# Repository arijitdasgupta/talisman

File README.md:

# Talisman

In at attempt to teach myself how to design PCBs, I made this trinket thingie to share with my friends. The board runs RP2040, and I am going to make some games for it.

## Games that run on this

 - [Bike w Friends](https://github.com/arijitdasgupta/bike_w_friends/)
 - [Flappy Mycologist](https://github.com/arijitdasgupta/flappy_mycologist)

## Features

 - I2C SSD1306 based display
 - Raspberry Pi Pico brain
 - 3 x buttons
 - Shared power between battery & USB
 - Battery charging
 - 3D printable case

## Notes

The manufacturing process with PCB makers such as JLCPCB is a little convoluted, even though I added BOM, drills and rotation files those may not be usable for you. But the general schematic designs and part ids should be helpful if you decide to make one yourself. If you have any questions, do drop a note. I have purposefully omitted writing a build guide for this very reason, but I am happy to write on up if anyone needs it.

## TODO
 - Write assembly instructions

## What's Friday Makers Club?

TODO

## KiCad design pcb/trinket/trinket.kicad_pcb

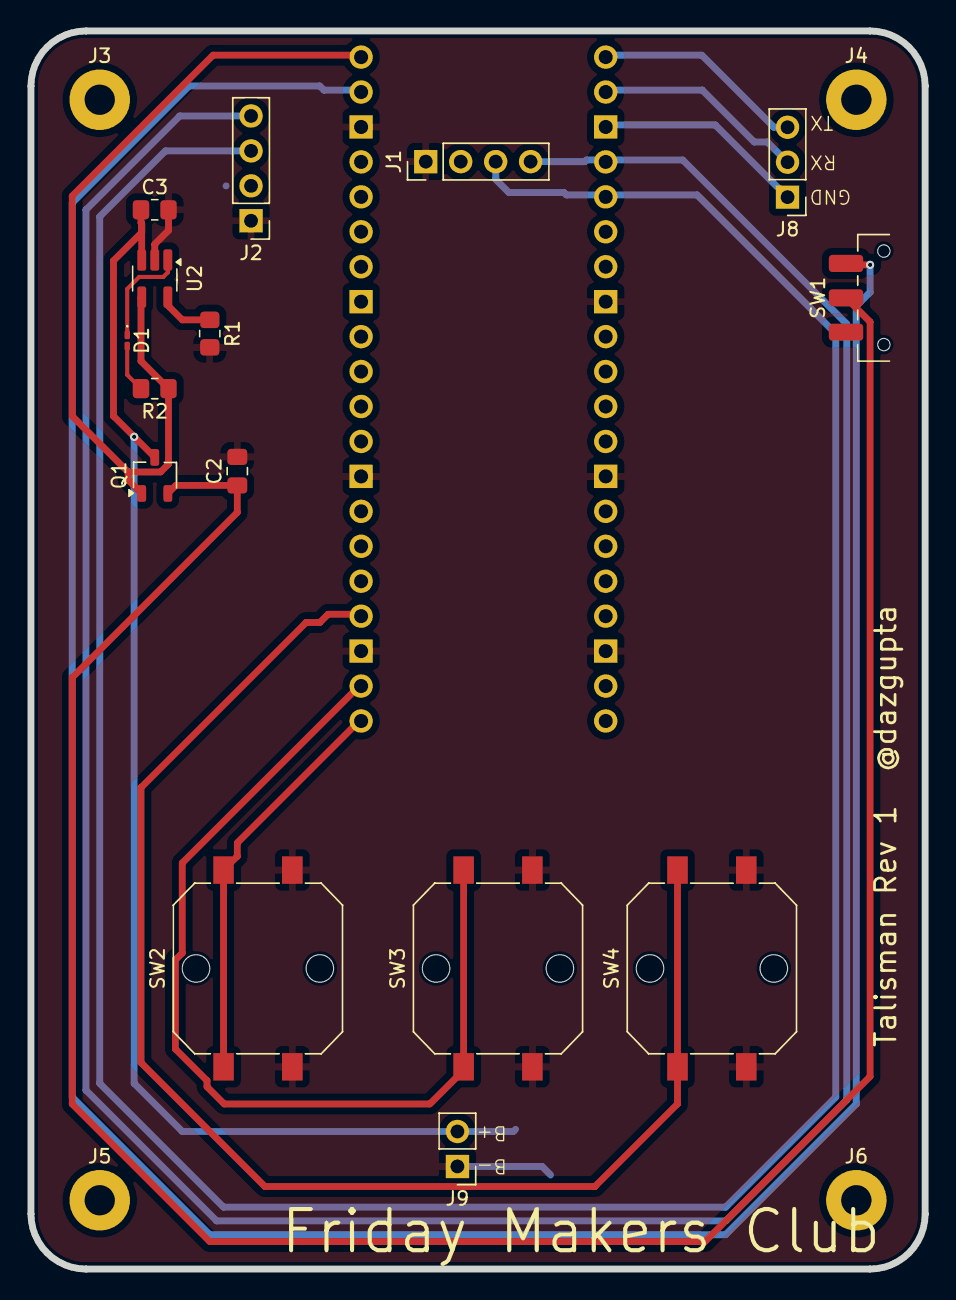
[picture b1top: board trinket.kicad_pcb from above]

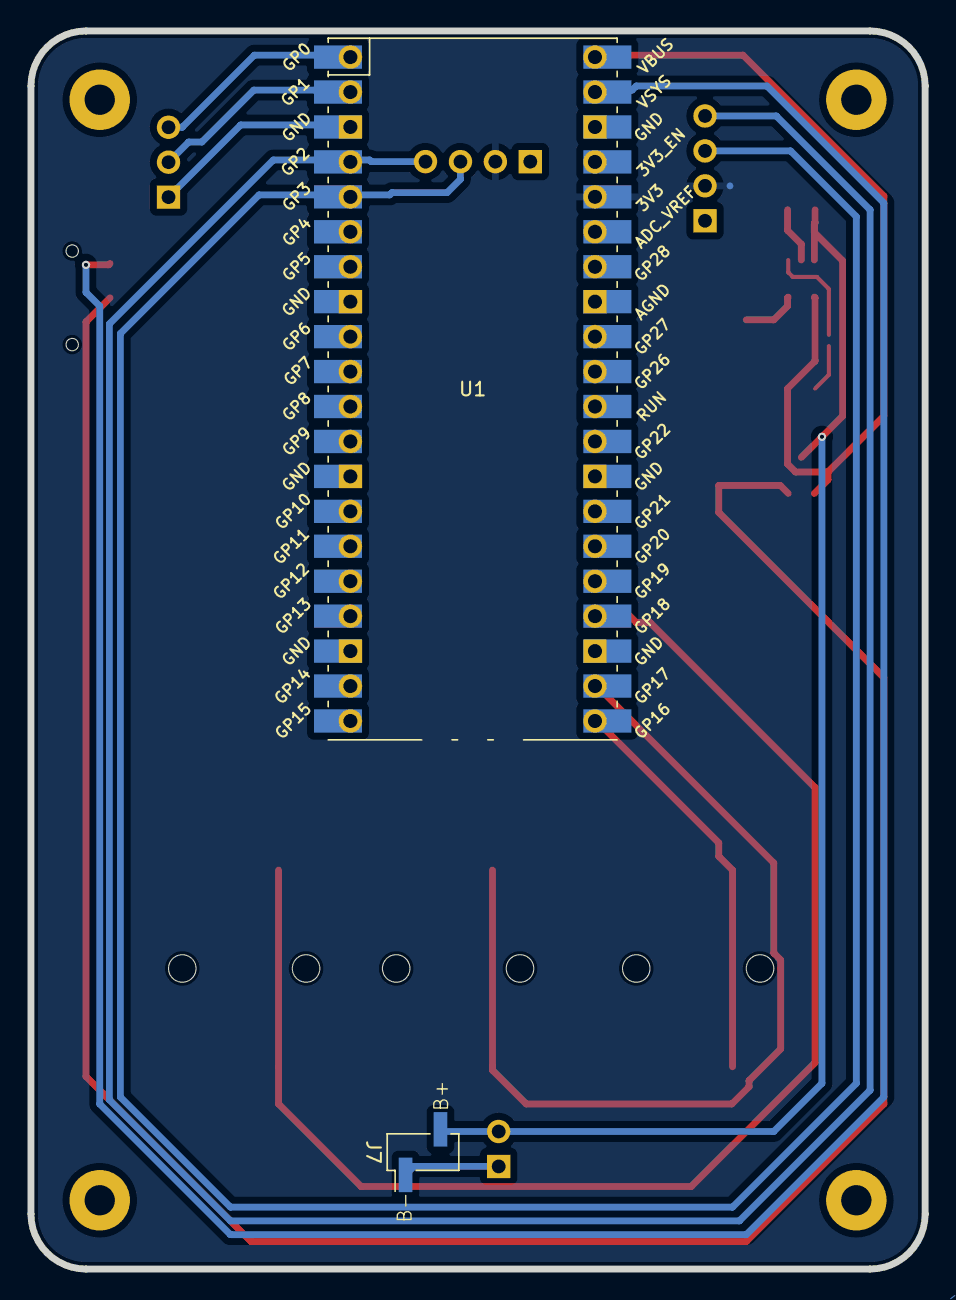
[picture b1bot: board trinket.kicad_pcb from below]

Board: 2 copper layers, 65.0 x 90.0 mm, 21 parts (2 on the bottom side), 17 nets.

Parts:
C2: 1u; C_0805_2012Metric_Pad1.18x1.45mm_HandSolder
C3: 4u7; R_0805_2012Metric_Pad1.20x1.40mm_HandSolder
D1: LED; LED_0201_0603Metric_Pad0.64x0.40mm_HandSolder
J1: OLED2; PinHeader_1x04_P2.54mm_Vertical
J2: OLED1; PinHeader_1x04_P2.54mm_Vertical
J3: MountingHole1; MountingHole_2.2mm_M2_Pad
J4: MountingHole2; MountingHole_2.2mm_M2_Pad
J5: MountingHole3; MountingHole_2.2mm_M2_Pad
J6: MountingHole4; MountingHole_2.2mm_M2_Pad
J7: BATT
J8: DEBUG_UART; PinHeader_DEBUG
J9: BATT_ALT; BATT_TH
Q1: DMP1045U; TSOT-23
R1: 10K; R_0805_2012Metric_Pad1.20x1.40mm_HandSolder
R2: 470; R_0805_2012Metric_Pad1.20x1.40mm_HandSolder
SW1: SW_SPDT; SW_SPDT_CK_JS102011SAQN
SW2: Left; SW_Push_1P1T_NO_CK_PTS125Sx43PSMTR
SW3: Center; SW_Push_1P1T_NO_CK_PTS125Sx43PSMTR
SW4: Right; SW_Push_1P1T_NO_CK_PTS125Sx43PSMTR
U1: Pico; RPi_Pico_SMD_TH
U2: MCP73831T-2ACI_OT; SOT-23-5_HandSoldering

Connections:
+3V3: J1.2, J2.2, U1.36 (3V3)
BTCENTER: SW3.1, U1.22 (GPIO17)
BTLEFT: SW2.1, U1.21 (GPIO16)
BTRIGHT: SW4.1, U1.24 (GPIO18)
GND: C2.2, C3.2, J1.1, J2.1, J7.1 (B-), J9.1 (B-), R1.2, SW2.2, SW3.2, SW4.2, U1.8 (GND), U1.13 (GND), U1.18 (GND), U1.23 (GND), U1.28 (GND), U1.38 (GND), U2.2 (VSS)
unnamed: D1.2 (A), R2.2
unnamed: D1.1 (K), U2.1 (STAT)
unnamed: J8.1 (GND), U1.3 (GND)
unnamed: J8.2 (RX), U1.2 (GPIO1)
unnamed: J8.3 (TX), U1.1 (GPIO0)
unnamed: C2.1, Q1.2, SW1.2 (B)
unnamed: R1.1, U2.5 (PROG)
OLED_SCL: J1.3, J2.3, U1.5 (GPIO3)
OLED_SDA: J1.4, J2.4, U1.4 (GPIO2)
VBAT+: C3.1, J7.2 (B+), J9.2 (B+), Q1.3, U2.3 (VBAT)
VSYS: SW1.3 (C), U1.39 (VSYS)
VUSB: Q1.1, R2.1, U1.40 (VBUS), U2.4 (VDD)

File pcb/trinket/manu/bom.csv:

"Comment","Designator","Footprint","LCSC Part Number"
"OLED2","J1","",""
"OLED1","J2","",""
"MountingHole1","J3","",""
"MountingHole2","J4","",""
"MountingHole3","J5","",""
"MountingHole4","J6","",""
"BATT","J7","",""
"DEBUG_UART","J8","",""
"BATT_ALT","J9","",""
"Pico","U1","",""
"LED","D1","0603","C2286"
"1u","C2","0805","C1712"
"4u7","C3","0805","C1746"
"10K","R1","0805","C149881"
"470","R2","0805","C21266"
"Left","SW2","C318915","C318915"
"Center","SW3","C318915","C318915"
"Right","SW4","C318915","C318915"
"SW_SPDT","SW1","SMD","C92658"
"DMP1045U","Q1","SOT-23","C177033"
"MCP73831T-2ACI_OT","U2","SOT-23-5","C424093"

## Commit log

2024-11-09 fix case dimensions
2024-11-10 Add image
2024-11-26 update KiCAD stuff
